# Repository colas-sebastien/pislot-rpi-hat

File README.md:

# PiSlot Raspberry Hat

## WARNING: NOT TESTED (yet)
The PiSlot Raspberry hat is not tested for the moment.

https://pislot.net

## Kicad electronic diagram

## Kicad PCB

## Libraries

You will probably have to use the following libraries:

- https://raw.githubusercontent.com/xesscorp/RPi_Hat_Template/master/RPi_Hat-cache.lib

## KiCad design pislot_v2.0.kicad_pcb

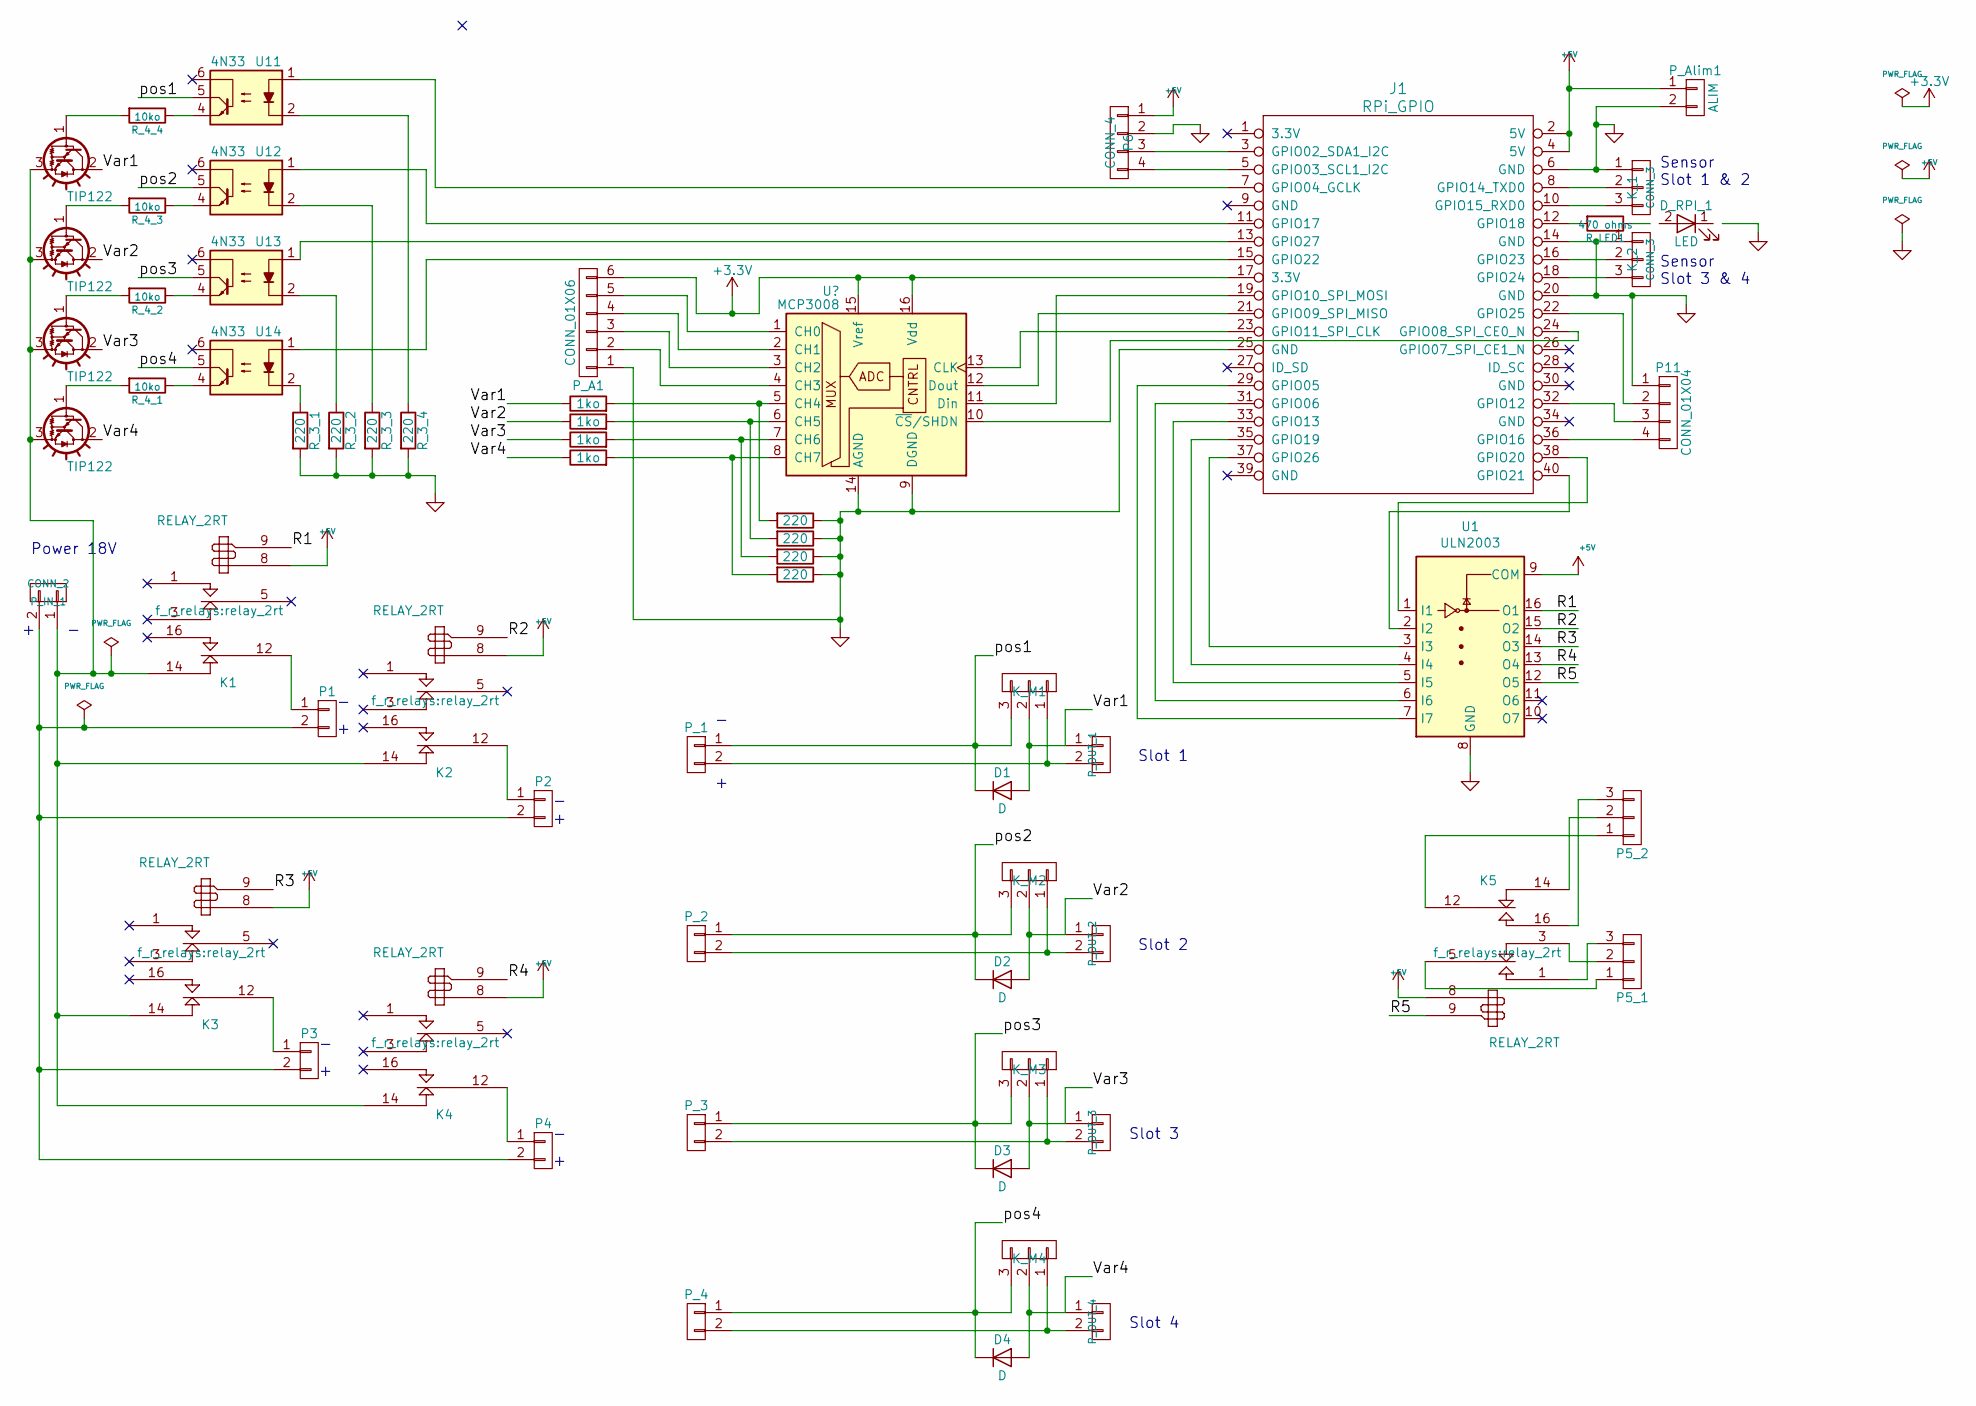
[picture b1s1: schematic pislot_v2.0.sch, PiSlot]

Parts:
D1, D2, D3, D4: D; Diode_DO-41_SOD81_Horizontal_RM10
D_RPI_1: LED; LED-5MM
J1: RPi_GPIO; Pin_Header_Straight_2x20
K1, K2, K3, K4, K5: RELAY_2RT; relay_2rt
K_1, K_2: CONN_3; Pin_Header_Straight_1x03
K_M1, K_M2, K_M3, K_M4: CONN_3; Socket_MOLEX-KK-RM2-54mm_Lock_3pin_straight
P1, P2, P3, P4: CONN_01X02; Socket_MOLEX-KK-RM2-54mm_Lock_2pin_straight
P5_1, P5_2: C3; Socket_MOLEX-KK-RM2-54mm_Lock_3pin_straight
P6: CONN_4; Pin_Header_Straight_1x04
P11: CONN_01X04; Pin_Header_Straight_1x04
P_1, P_2, P_3, P_4: CONN_01X02; Socket_MOLEX-KK-RM2-54mm_Lock_2pin_straight
P_A1: CONN_01X06; Pin_Header_Straight_1x06
P_Alim1: ALIM; Pin_Header_Straight_1x02
P_IN_1: CONN_2; Socket_MOLEX-KK-RM2-54mm_Lock_2pin_straight
P_OUT_1, P_OUT_2, P_OUT_3, P_OUT_4: CONN_2; Socket_MOLEX-KK-RM2-54mm_Lock_2pin_straight
Q1, Q2, Q3, Q4: TIP122; TO-220_Neutral123_Vertical
R_1_1, R_1_2, R_1_3, R_1_4: 1ko; Resistor_Horizontal_RM10mm
R_2_1, R_2_2, R_2_3, R_2_4, R_3_1, R_3_2, R_3_3, R_3_4: 220; Resistor_Horizontal_RM10mm
R_4_1, R_4_2, R_4_3, R_4_4: 10ko; Resistor_Horizontal_RM10mm
R_LED1: 470 ohms; Resistor_Horizontal_RM15mm
U1: ULN2003
U11, U12, U13, U14: 4N33; DIP-6_W7.62mm

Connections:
+3V3: J1.17 (3.3V), P_A1.6; also elsewhere on the board
+5V: J1.2 (5V), J1.4 (5V), K1.8, K2.8, K3.8, K4.8, K5.8, P6.1, P_Alim1.1, U1.9 (COM)
/R1: K1.9, U1.16 (O1)
/R2: K2.9, U1.15 (O2)
/R3: K3.9, U1.14 (O3)
/R4: K4.9, U1.13 (O4)
/R5: K5.9, U1.12 (O5)
/Var1: D1.2 (A), K_M1.2, P_OUT_1.1, Q1.2 (C), R_1_1.1
/Var2: D2.2 (A), K_M2.2, P_OUT_2.1, Q2.2 (C), R_1_2.1
/Var3: D3.2 (A), K_M3.2, P_OUT_3.1, Q3.2 (C), R_1_3.1
/Var4: D4.2 (A), K_M4.2, P_OUT_4.1, Q4.2 (C), R_1_4.1
/pos1: D1.1 (K), K_M1.3, P_1.1, U11.5
/pos2: D2.1 (K), K_M2.3, P_2.1, U12.5
/pos3: D3.1 (K), K_M3.3, P_3.1, U13.5
/pos4: D4.1 (K), K_M4.3, P_4.1, U14.5
GND: D_RPI_1.1 (K), J1.6 (GND), J1.14 (GND), J1.20 (GND), J1.25 (GND), K_1.1, K_2.1, P6.2, P11.1, P_A1.1, P_Alim1.2, R_2_1.1, R_2_2.1, R_2_3.1, R_2_4.1, R_3_1.2, R_3_2.2, R_3_3.2, R_3_4.2, U1.8 (GND); also elsewhere on the board
unnamed: D_RPI_1.2 (A), R_LED1.1
unnamed: J1.3 (GPIO02_SDA1_I2C), P6.3
unnamed: J1.5 (GPIO03_SCL1_I2C), P6.4
unnamed: J1.7 (GPIO04_GCLK), U11.1
unnamed: J1.8 (GPIO14_TXD0), K_1.2
unnamed: J1.10 (GPIO15_RXD0), K_1.3
unnamed: J1.11 (GPIO17), U12.1
unnamed: J1.12 (GPIO18), R_LED1.2
unnamed: J1.13 (GPIO27), U13.1
unnamed: J1.15 (GPIO22), U14.1
unnamed: J1.16 (GPIO23), K_2.2
unnamed: J1.18 (GPIO24), K_2.3
unnamed 30: J1.19 (GPIO10_SPI_MOSI); also elsewhere on the board
unnamed 31: J1.21 (GPIO09_SPI_MISO); also elsewhere on the board
unnamed: J1.22 (GPIO25), P11.2
unnamed 33: J1.23 (GPIO11_SPI_CLK); also elsewhere on the board
unnamed 34: J1.24 (GPIO08_SPI_CE0_N); also elsewhere on the board
unnamed: J1.29 (GPIO05), U1.7 (I7)
unnamed: J1.31 (GPIO06), U1.6 (I6)
unnamed: J1.32 (GPIO12), P11.3
unnamed: J1.33 (GPIO13), U1.5 (I5)
unnamed: J1.35 (GPIO19), U1.4 (I4)
unnamed: J1.36 (GPIO16), P11.4
unnamed: J1.37 (GPIO26), U1.3 (I3)
unnamed: J1.38 (GPIO20), U1.1 (I1)
unnamed: J1.40 (GPIO21), U1.2 (I2)
unnamed: K1.12 (C2), P1.1
unnamed: K1.14 (R2), K2.14 (R2), K3.14 (R2), K4.14 (R2), P_IN_1.1, Q1.3 (E), Q2.3 (E), Q3.3 (E), Q4.3 (E)
unnamed: K2.12 (C2), P2.1
unnamed: K3.12 (C2), P3.1
unnamed: K4.12 (C2), P4.1
unnamed: K5.1 (T1), P5_1.3
unnamed: K5.3 (R1), P5_1.2
unnamed: K5.5 (C1), P5_1.1
unnamed: K5.12 (C2), P5_2.1
unnamed: K5.14 (R2), P5_2.2
unnamed: K5.16 (T2), P5_2.3
unnamed: K_M1.1, P_1.2, P_OUT_1.2
unnamed: K_M2.1, P_2.2, P_OUT_2.2
unnamed: K_M3.1, P_3.2, P_OUT_3.2
unnamed: K_M4.1, P_4.2, P_OUT_4.2
unnamed: P1.2, P2.2, P3.2, P4.2, P_IN_1.2
unnamed 82: P_A1.2; also elsewhere on the board
unnamed 83: P_A1.3; also elsewhere on the board
unnamed 84: P_A1.4; also elsewhere on the board
unnamed 85: P_A1.5; also elsewhere on the board
unnamed: Q1.1 (B), R_4_4.2
unnamed: Q2.1 (B), R_4_3.2
unnamed: Q3.1 (B), R_4_2.2
unnamed: Q4.1 (B), R_4_1.2
unnamed 90: R_1_1.2, R_2_1.2; also elsewhere on the board
unnamed 91: R_1_2.2, R_2_2.2; also elsewhere on the board
unnamed 92: R_1_3.2, R_2_3.2; also elsewhere on the board
unnamed 93: R_1_4.2, R_2_4.2; also elsewhere on the board
unnamed: R_3_1.1, U14.2
unnamed: R_3_2.1, U13.2
unnamed: R_3_3.1, U12.2
unnamed: R_3_4.1, U11.2
unnamed: R_4_1.1, U14.4
unnamed: R_4_2.1, U13.4
unnamed: R_4_3.1, U12.4
unnamed: R_4_4.1, U11.4

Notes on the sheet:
Slot 1
Slot 2
Slot 3
Slot 4
Power 18V
Sensor Slot 1 & 2
Sensor Slot 3 & 4

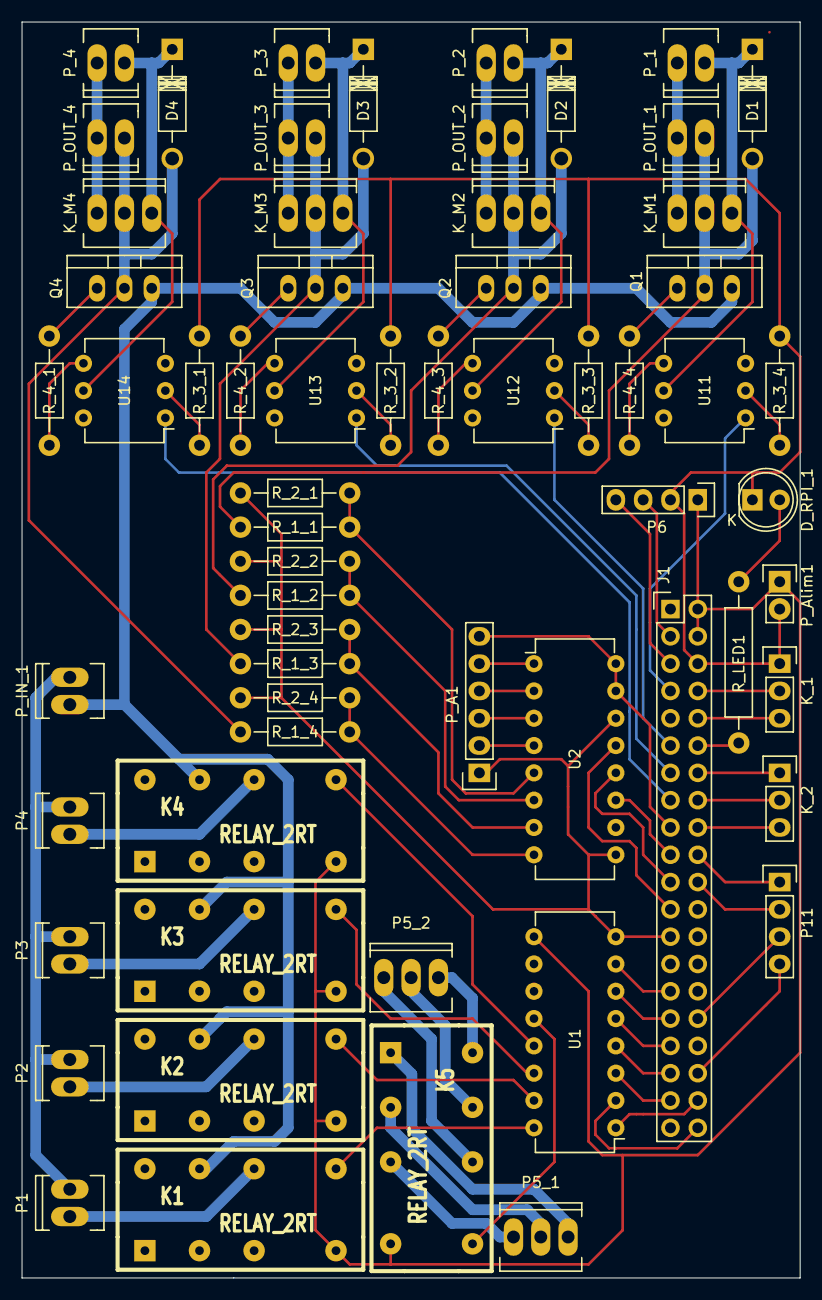
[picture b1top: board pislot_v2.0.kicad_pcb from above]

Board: 2 copper layers, 72.4 x 116.8 mm, 63 parts (0 on the bottom side), 78 nets.

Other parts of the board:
U2: MCP3008; DIP-16_W7.62mm

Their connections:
+3V3: U2.15, U2.16; also elsewhere on the board
GND: U2.9, U2.14; also elsewhere on the board
unnamed 30: U2.11; also elsewhere on the board
unnamed 31: U2.12; also elsewhere on the board
unnamed 33: U2.13; also elsewhere on the board
unnamed 34: U2.10; also elsewhere on the board
unnamed 82: U2.4; also elsewhere on the board
unnamed 83: U2.3; also elsewhere on the board
unnamed 84: U2.2; also elsewhere on the board
unnamed 85: U2.1; also elsewhere on the board
unnamed 90: U2.5; also elsewhere on the board
unnamed 91: U2.6; also elsewhere on the board
unnamed 92: U2.7; also elsewhere on the board
unnamed 93: U2.8; also elsewhere on the board

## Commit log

2020-08-22 Version 2.0
2020-08-22 disclamer
